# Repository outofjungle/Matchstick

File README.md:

# Matchstick
# Matchstick
# Matchstick

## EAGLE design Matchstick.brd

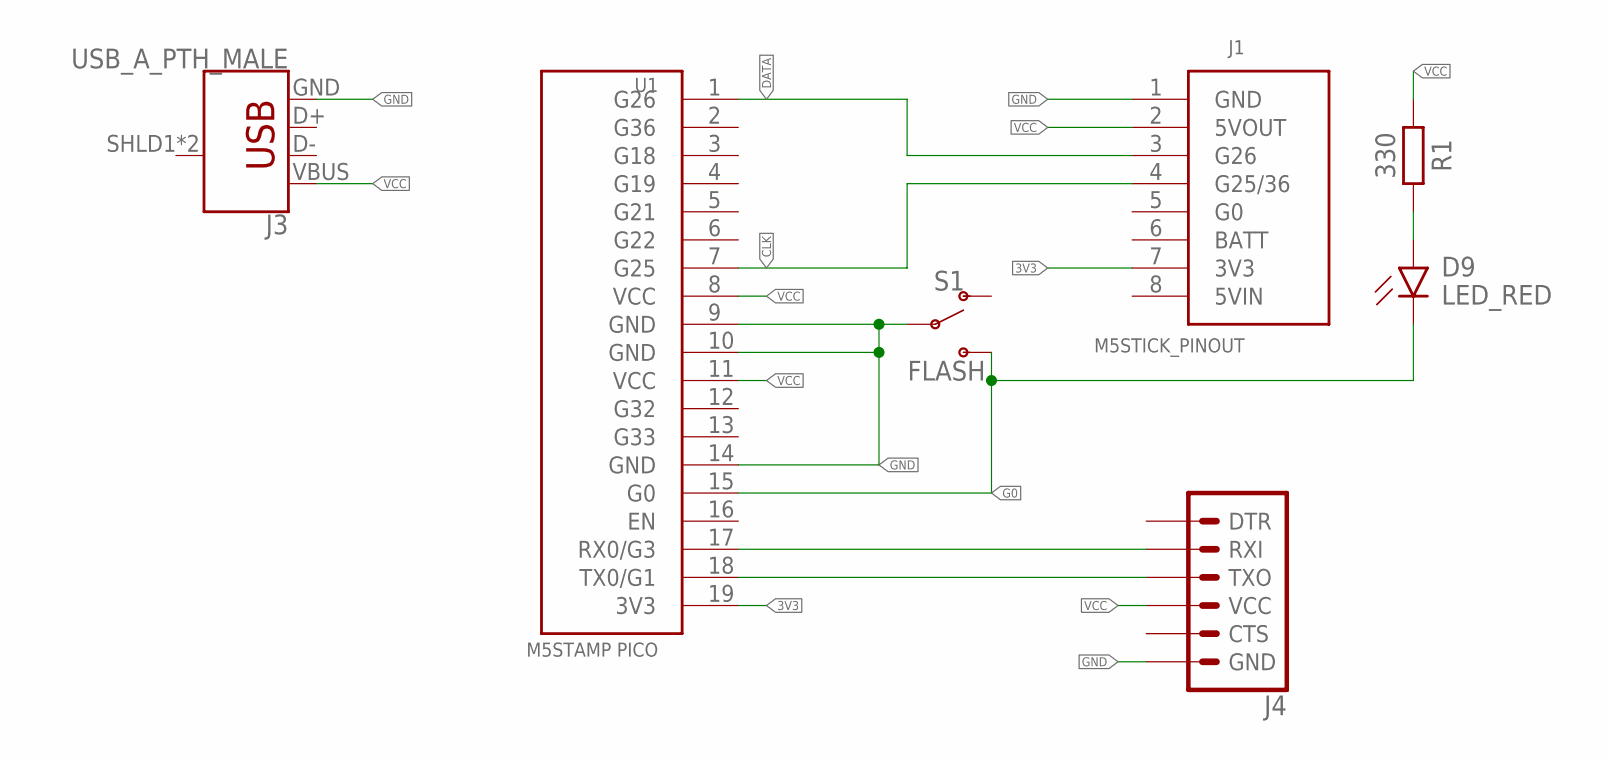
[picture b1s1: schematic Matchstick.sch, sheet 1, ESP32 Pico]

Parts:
D9: LED_RED; LEDC2012X105N_RND-R
J1: M5STICK_PINOUT
J3: USB_A_PTH_MALE; USB-A-H
J4: 6_PIN_SERIAL_TARGETSILK; 6_PIN_SERIAL_TARGET_SIDE_W_SILK
R1: 330; RESC2012X65
S1: FLASH; SWITCH_SPST_SMD_A
U1: M5STAMP PICO; M5STAMP-PICO

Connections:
3V3: J1.7 (3V3), U1.19 (3V3)
CLK: J1.4 (G25/36), U1.7 (G25); also elsewhere on the board
DATA: J1.3 (G26), U1.1 (G26); also elsewhere on the board
G0: D9.C, S1.3 (S), U1.15 (G0)
GND: J1.1 (GND), J3.GND, J4.P$6 (GND), S1.2, U1.9 (GND), U1.10 (GND), U1.14 (GND); also elsewhere on the board
LED_PWR: D9.A, R1.2
RX: J4.P$3 (RXI), U1.17 (RX0/G3)
TX: J4.P$2 (TXO), U1.18 (TX0/G1)
VCC: J1.2 (5VOUT), J3.VBUS, J4.P$4 (VCC), R1.1, U1.8 (VCC), U1.11 (VCC); also elsewhere on the board

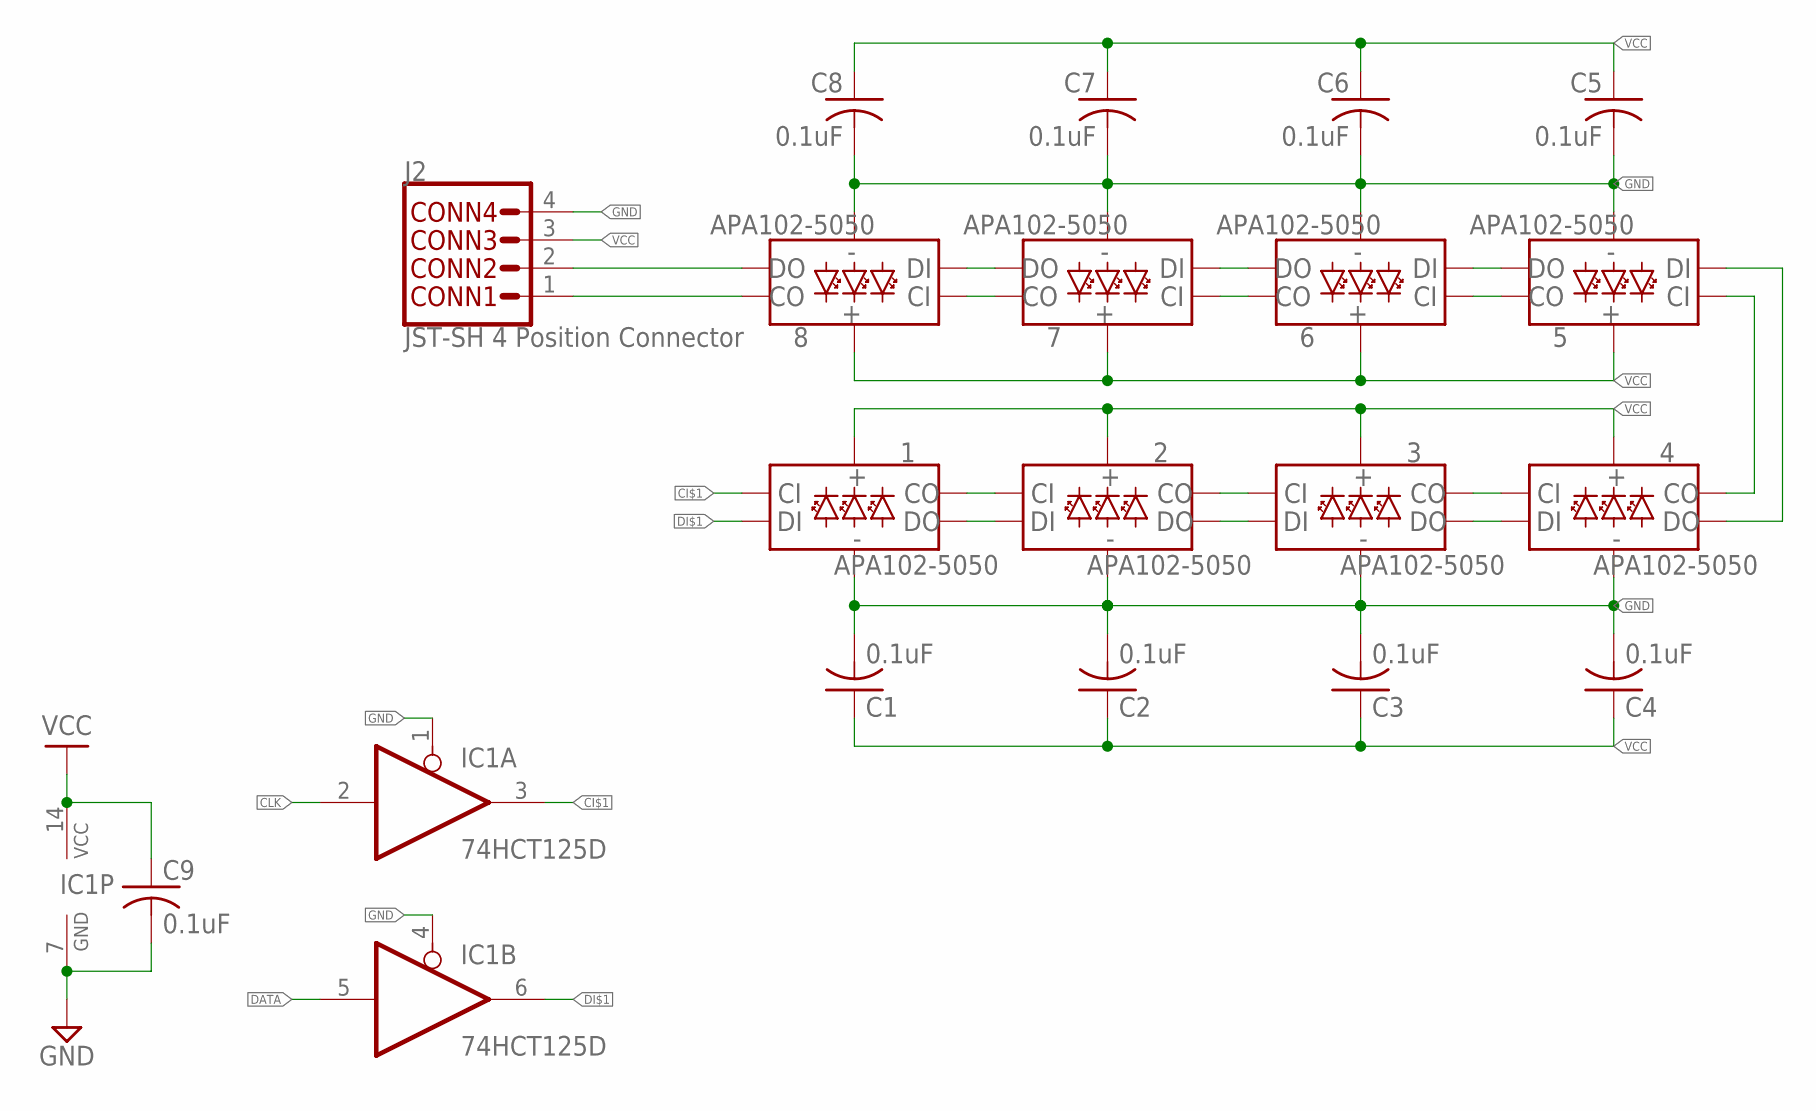
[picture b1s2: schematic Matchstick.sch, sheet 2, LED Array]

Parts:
1, 2, 3, 4, 5, 6, 7, 8: APA102-5050
C1, C2, C3, C4, C5, C6, C7, C8, C9: 0.1uF; CAPC2012X110
IC1: 74HCT125D; SO14
J2: JST-SH 4 Position Connector; JST04_1MM_RA

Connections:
CI$1: 1.P2 (CI), IC1.3 (O)
CI$2: 1.P5 (CO), 2.P2 (CI)
CI$3: 2.P5 (CO), 3.P2 (CI)
CI$4: 3.P5 (CO), 4.P2 (CI)
CI$5: 4.P5 (CO), 5.P2 (CI)
CI$6: 5.P5 (CO), 6.P2 (CI)
CI$7: 6.P5 (CO), 7.P2 (CI)
CI$8: 7.P5 (CO), 8.P2 (CI)
CLK: IC1.2 (I); also elsewhere on the board
CO: 8.P5 (CO), J2.1
DATA: IC1.5 (I); also elsewhere on the board
DI$1: 1.P1 (DI), IC1.6 (O)
DI$2: 1.P6 (DO), 2.P1 (DI)
DI$3: 2.P6 (DO), 3.P1 (DI)
DI$4: 3.P6 (DO), 4.P1 (DI)
DI$5: 4.P6 (DO), 5.P1 (DI)
DI$6: 5.P6 (DO), 6.P1 (DI)
DI$7: 6.P6 (DO), 7.P1 (DI)
DI$8: 7.P6 (DO), 8.P1 (DI)
DO: 8.P6 (DO), J2.2
GND: 1.P3 (GND), 2.P3 (GND), 3.P3 (GND), 4.P3 (GND), 5.P3 (GND), 6.P3 (GND), 7.P3 (GND), 8.P3 (GND), C1.2, C2.2, C3.2, C4.2, C5.2, C6.2, C7.2, C8.2, C9.2, IC1.1 (OE), IC1.4 (OE), IC1.7 (GND), J2.4; also elsewhere on the board
VCC: 1.P4 (VCC), 2.P4 (VCC), 3.P4 (VCC), 4.P4 (VCC), 5.P4 (VCC), 6.P4 (VCC), 7.P4 (VCC), 8.P4 (VCC), C1.1, C2.1, C3.1, C4.1, C5.1, C6.1, C7.1, C8.1, C9.1, IC1.14 (VCC), J2.3; also elsewhere on the board

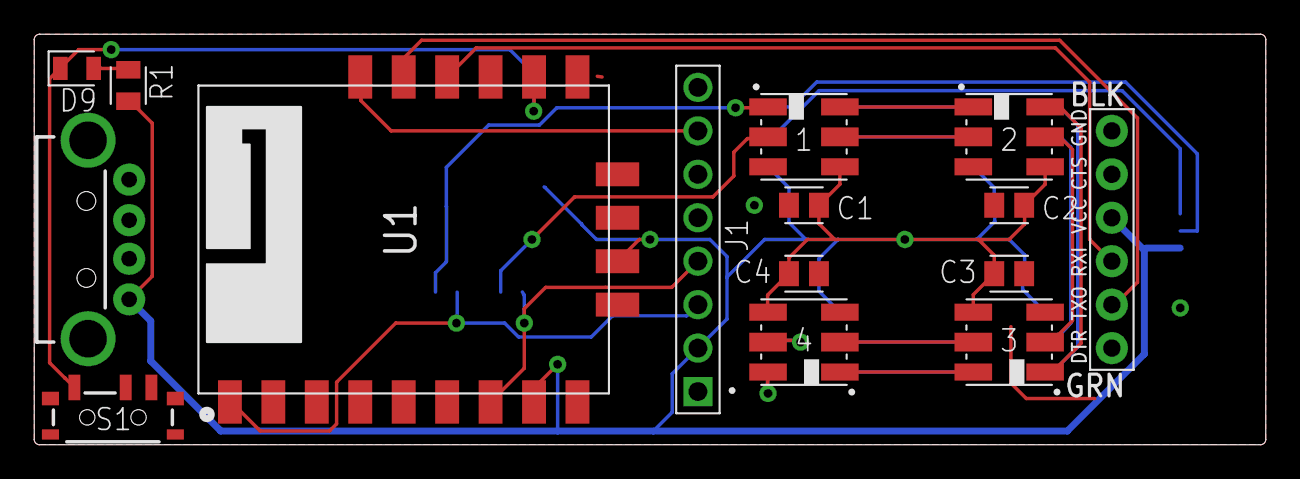
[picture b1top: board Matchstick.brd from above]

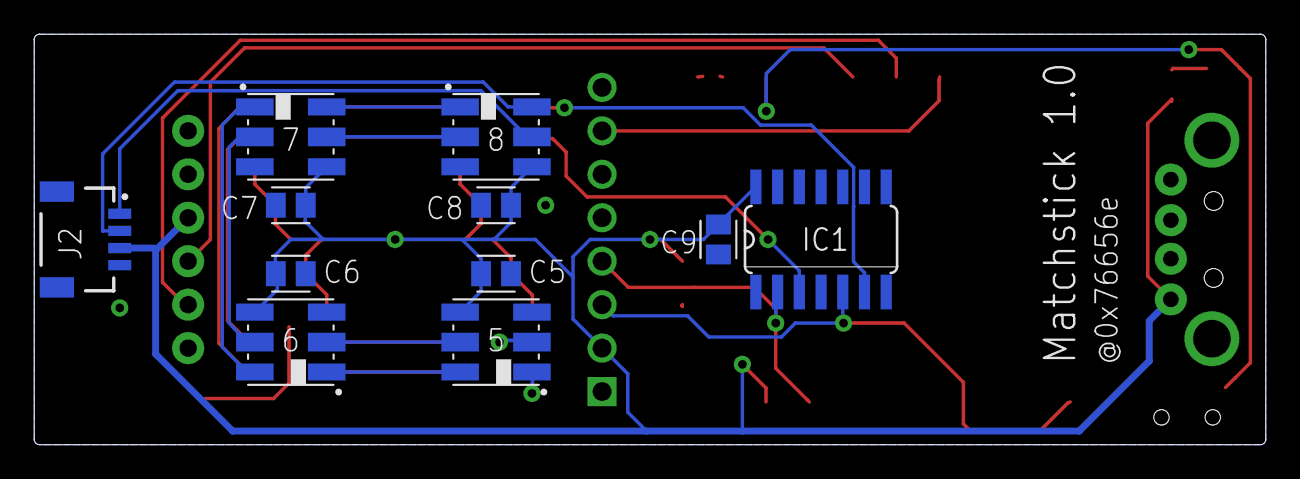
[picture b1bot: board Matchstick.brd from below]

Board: 2 copper layers, 72.0 x 24.0 mm, 26 parts (11 on the bottom side), 27 nets.

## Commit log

2022-02-01 fixed silkscreen for all components
2022-02-02 V1.0 final
2022-02-16 Fixing RX/TX cross-wire

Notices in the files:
parts and their libraries:
SparkFun-LED: Licensing: Creative Commons ShareAlike 4.0 International - https://creativecommons.org/licenses/by-sa/4.0
